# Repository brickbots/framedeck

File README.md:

# framedeck

A Cyberdeck built with the framework mainboard.  

[Framework](https://frame.work) has 
created a really slick, fully user servicable, laptop and have recently started selling the 
[mainboard](https://frame.work/marketplace/mainboards) as a SBC for general 
use.  To better support folks who may want to integrate it into their projects, they are also 
releasing [technical documentation](https://github.com/FrameworkComputer/Mainboard) including 
pinouts, cad models and other resources.

As they were preparing this documentation release, they emailed me to see if I'd be interested
in a collaboration of sorts.  They would provide one of their laptops and some additional modules
for me to build something unique with the only condition being that I released the designs 
for public use.  So here we are!

The mainboard is a great little unit, being a full Intel based system on a single board with 
great storage and memory expansion, decent on-board graphics and full power management.  Since
it was designed to fit into the laptop first and foremost, some of the connectors are fairly
specialized, but with the pinouts available there are a lot of opportunities for expansion. The
board also has four standard USB-C ports which provide many possibilities without even trying
any of the other on-board connectors.

That's all to say that when they reached out and explained their plans and offered to let 
me play with one, I jumped at the chance and this is what I came up with after some experimentation.

It's my take on the slab style computers that were somewhat popular before the world settled
on clamshell designs for portable computers.  I really wanted a 
[TRS-80 model 100](https://en.wikipedia.org/wiki/TRS-80_Model_100) when I was young so this
sort of design was a big influence.

To complete the unit I added battery from the framework laptop, custom mechanical keyboard, wifi card, 
ssd storage, 16gb of memory, 7" IPS display and some speakers in the hopes of making a fairly useful 
computer.  I ended up using the mainboard with their battery rather than roll my own power solution as
it has solid capacity and is already desinged to work with the onboard power management.  For
other uses the mainboard can be powered via USB-C, so a solid powerbank would provide plenty 
of runtime or it can run off any USB-C power brick for stationary use.

For the case, I wanted something interesting that showed off the mainboard, custom keyboard PCB and 
just looked unusual... so clear acrylic and brass won the day!  I thought about 3d printing, and 
I could have done it in several sections, but building the unit up with layers of laser-cut acrylic 
offered some interesting challenges and opportunities.  

Consider this repo a sort of 'guided tour' to give some inspiration and show what might be done with the
framework mainboard.  I'll highlight some things that I think are interesting, or that were tricky, but 
it's not meant to be a comprehensive guide so all the normal caveats apply if you
want to dive in and build something based off this material.  I'm including all of
my design files for reference, but there are lots of details of the build I probably won't cover.  
If you want to build one, or something similar, feel free to reach out and I'd be happy to answer
and questions or provide advice.

* [Build Tour](docs/build_tour.md)
* [Parts List](docs/parts.md)
* [Case Layers](case/layers.md)
* [3d Printed Bits](printed_parts/bits.md)
* [What's with that keyboard?](docs/keyboard.md)

## Copyright and License

Copyright (c) 2022 Richard Sutherland. All rights reserved.

All files are licensed under MIT license or [CC BY-SA 4.0](https://creativecommons.org/licenses/by-sa/4.0/), see the [LICENSE](LICENSE) for more information.

<a href='https://ko-fi.com/brickbots' target='_blank'>

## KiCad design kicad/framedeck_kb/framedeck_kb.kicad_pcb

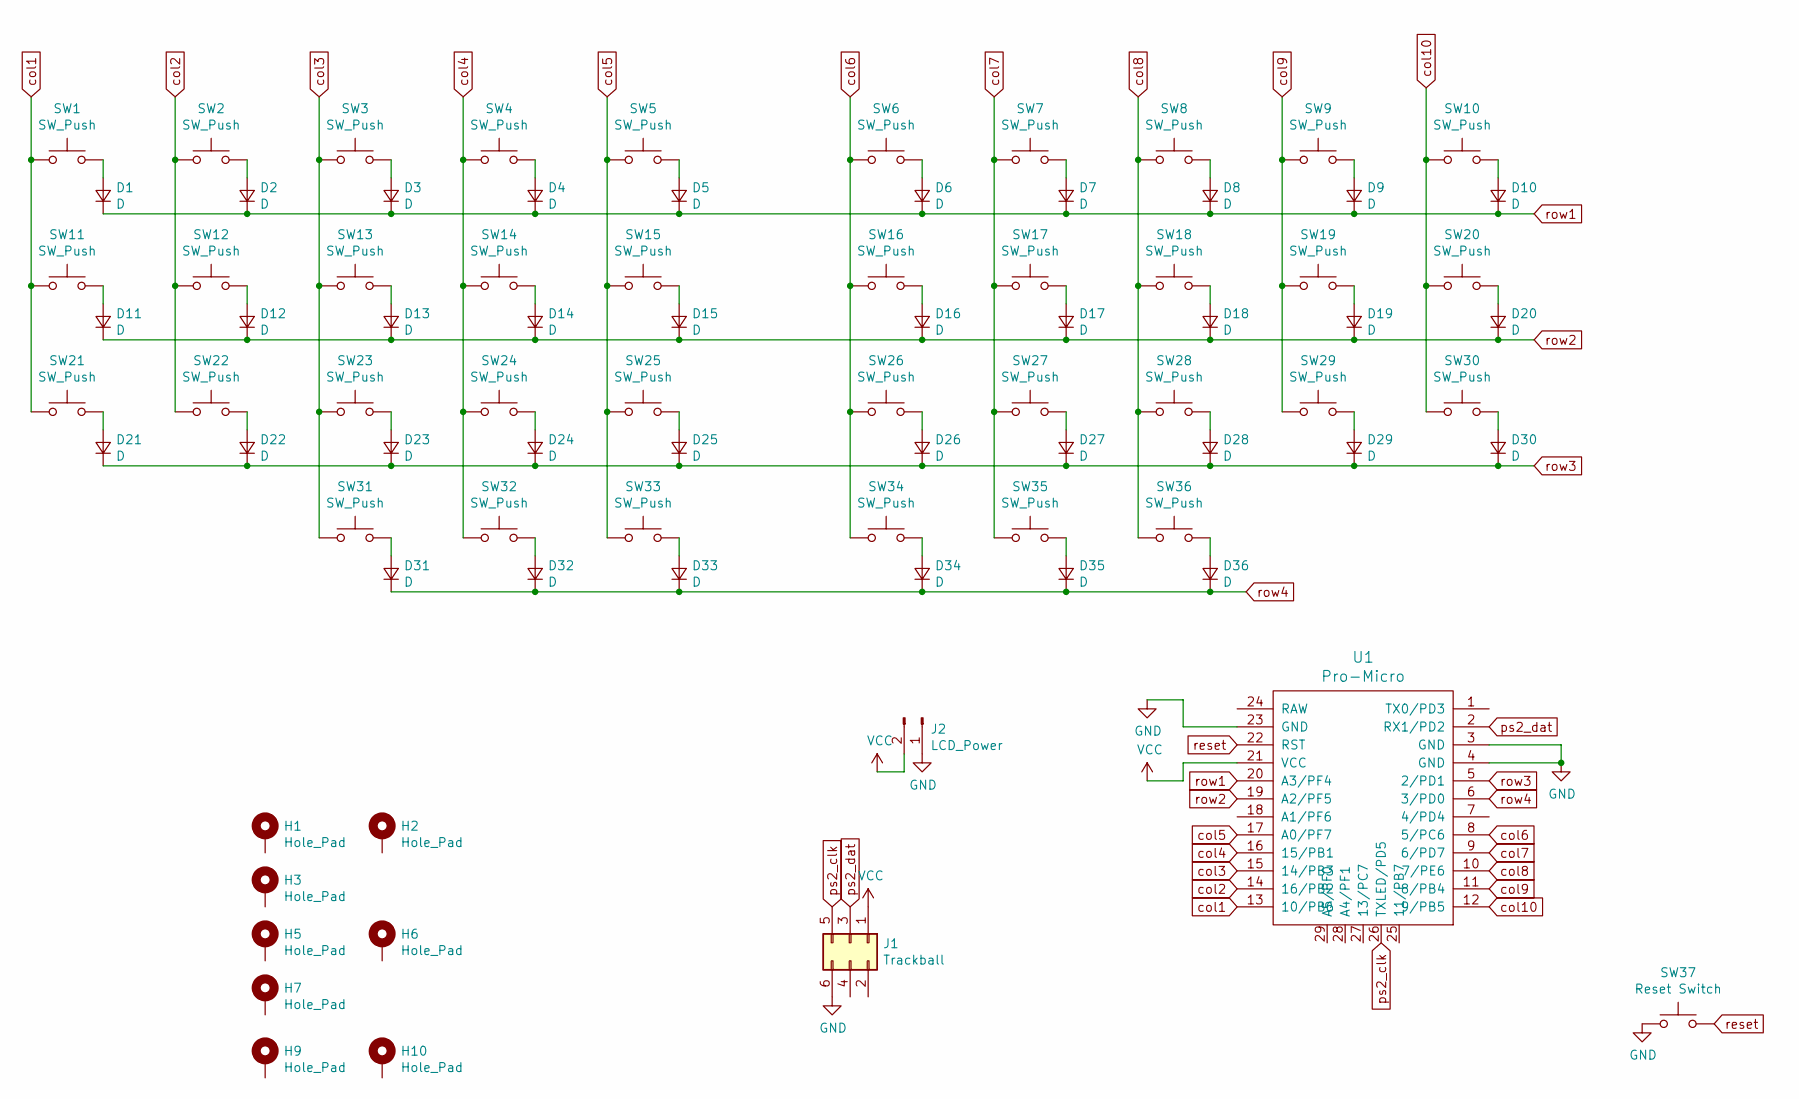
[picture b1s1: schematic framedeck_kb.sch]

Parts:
D1, D2, D3, D4, D5, D6, D7, D8, D9, D10, D11, D12, D13, D14, D15, D16, D17, D18, D19, D20, D21, D22, D23, D24, D25, D26, D27, D28, D29, D30, D31, D32, D33, D34, D35, D36: D; D_SOD-123
H1, H2, H3, H5, H6, H7, H9, H10: Hole_Pad; Mount_M2
J1: Trackball; PinHeader_2x03_P2.00mm_Vertical
J2: LCD_Power; PinHeader_1x02_P2.54mm_Vertical
SW1, SW2, SW3, SW4, SW5, SW6, SW7, SW8, SW9, SW10, SW11, SW12, SW13, SW14, SW15, SW16, SW17, SW18, SW19, SW20, SW21, SW22, SW23, SW24, SW25, SW26, SW27, SW28, SW29, SW30, SW31, SW32, SW33, SW34, SW35, SW36: SW_Push; SW_MX_plate
SW37: Reset Switch; SW_Push_6mm
U1: Pro-Micro; Elite-C

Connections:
GND: J1.6, J2.1, SW37.1, U1.3 (GND), U1.4 (GND), U1.23 (GND)
unnamed: D1.2 (A), SW1.2
unnamed: D2.2 (A), SW2.2
unnamed: D3.2 (A), SW3.2
unnamed: D4.2 (A), SW4.2
unnamed: D5.2 (A), SW5.2
unnamed: D6.2 (A), SW6.2
unnamed: D7.2 (A), SW7.2
unnamed: D8.2 (A), SW8.2
unnamed: D9.2 (A), SW9.2
unnamed: D10.2 (A), SW10.2
unnamed: D11.2 (A), SW11.2
unnamed: D12.2 (A), SW12.2
unnamed: D13.2 (A), SW13.2
unnamed: D14.2 (A), SW14.2
unnamed: D15.2 (A), SW15.2
unnamed: D16.2 (A), SW16.2
unnamed: D17.2 (A), SW17.2
unnamed: D18.2 (A), SW18.2
unnamed: D19.2 (A), SW19.2
unnamed: D20.2 (A), SW20.2
unnamed: D21.2 (A), SW21.2
unnamed: D22.2 (A), SW22.2
unnamed: D23.2 (A), SW23.2
unnamed: D24.2 (A), SW24.2
unnamed: D25.2 (A), SW25.2
unnamed: D26.2 (A), SW26.2
unnamed: D27.2 (A), SW27.2
unnamed: D28.2 (A), SW28.2
unnamed: D29.2 (A), SW29.2
unnamed: D30.2 (A), SW30.2
unnamed: D31.2 (A), SW31.2
unnamed: D32.2 (A), SW32.2
unnamed: D33.2 (A), SW33.2
unnamed: D34.2 (A), SW34.2
unnamed: D35.2 (A), SW35.2
unnamed: D36.2 (A), SW36.2
VCC: J1.1, J2.2, U1.21 (VCC)
col1: SW1.1, SW11.1, SW21.1, U1.13 (10/PB6)
col2: SW2.1, SW12.1, SW22.1, U1.14 (16/PB2)
col3: SW3.1, SW13.1, SW23.1, SW31.1, U1.15 (14/PB3)
col4: SW4.1, SW14.1, SW24.1, SW32.1, U1.16 (15/PB1)
col5: SW5.1, SW15.1, SW25.1, SW33.1, U1.17 (A0/PF7)
col6: SW6.1, SW16.1, SW26.1, SW34.1, U1.8 (5/PC6)
col7: SW7.1, SW17.1, SW27.1, SW35.1, U1.9 (6/PD7)
col8: SW8.1, SW18.1, SW28.1, SW36.1, U1.10 (7/PE6)
col9: SW9.1, SW19.1, SW29.1, U1.11 (8/PB4)
col10: SW10.1, SW20.1, SW30.1, U1.12 (9/PB5)
ps2_clk: J1.5, U1.26 (TXLED/PD5)
ps2_dat: J1.3, U1.2 (RX1/PD2)
reset: SW37.2, U1.22 (RST)
row1: D1.1 (K), D2.1 (K), D3.1 (K), D4.1 (K), D5.1 (K), D6.1 (K), D7.1 (K), D8.1 (K), D9.1 (K), D10.1 (K), U1.20 (A3/PF4)
row2: D11.1 (K), D12.1 (K), D13.1 (K), D14.1 (K), D15.1 (K), D16.1 (K), D17.1 (K), D18.1 (K), D19.1 (K), D20.1 (K), U1.19 (A2/PF5)
row3: D21.1 (K), D22.1 (K), D23.1 (K), D24.1 (K), D25.1 (K), D26.1 (K), D27.1 (K), D28.1 (K), D29.1 (K), D30.1 (K), U1.5 (2/PD1)
row4: D31.1 (K), D32.1 (K), D33.1 (K), D34.1 (K), D35.1 (K), D36.1 (K), U1.6 (3/PD0)

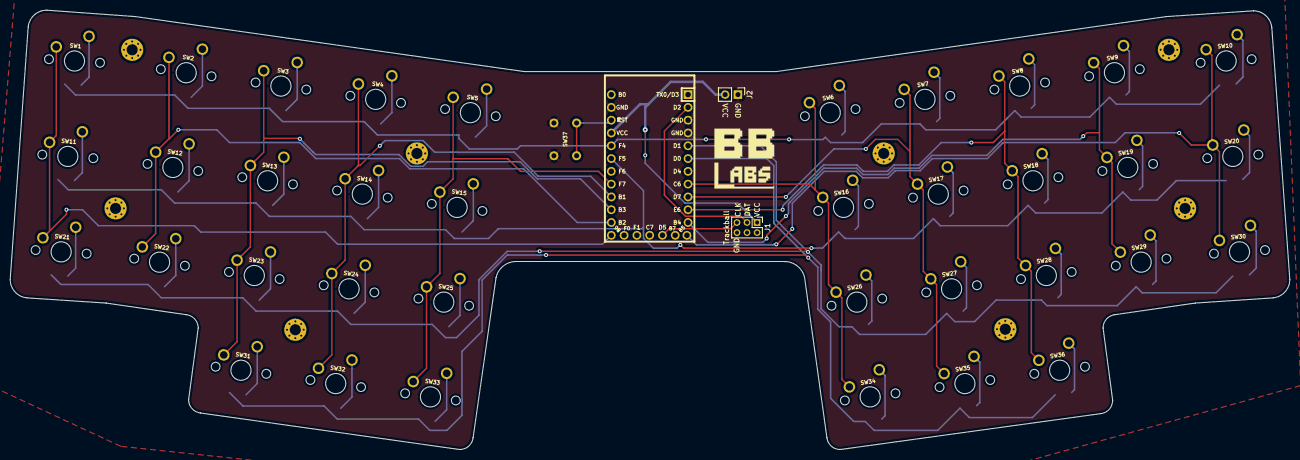
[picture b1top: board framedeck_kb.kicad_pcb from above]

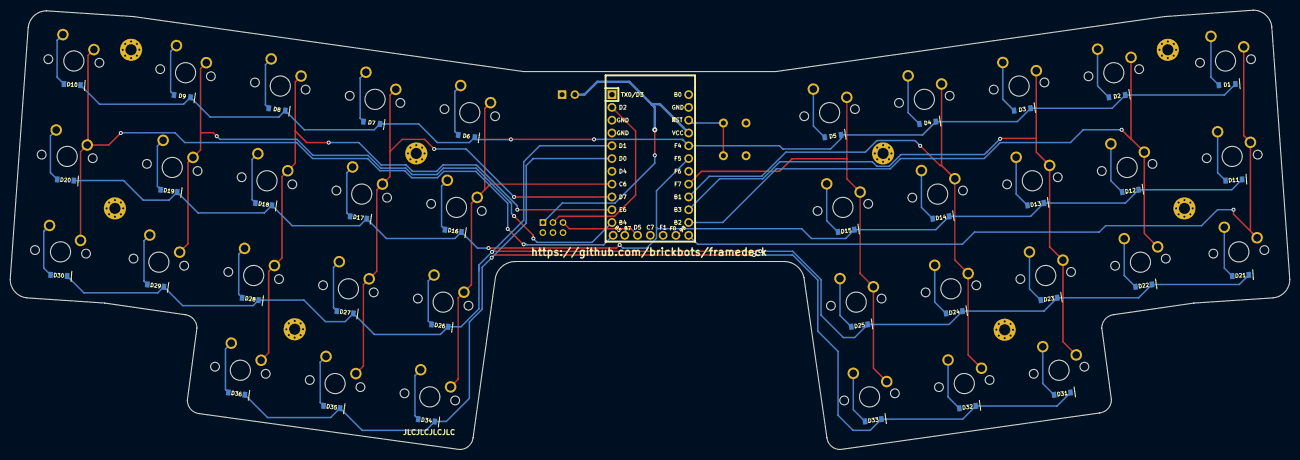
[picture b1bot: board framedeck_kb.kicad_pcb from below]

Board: 2 copper layers, 254.1 x 87.2 mm, 84 parts (37 on the bottom side), 55 nets.

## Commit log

2022-05-11 Starting docs
2022-05-11 Testing images
2022-05-11 Layers
2022-05-11 Fix layers
2022-05-11 Fix links in readme
2022-05-11 Continuing docs
2022-05-15 starting build guide
2022-05-15 Docs draft done
2022-05-15 Added printed docs
2022-05-15 Beauty images
2022-05-15 Fix readme image
2022-05-16 Typo fix s/obard/board
2022-05-16 Fix typos
2022-05-16 Update license for wikimedia friendliness
2022-05-19 Add keyboard info
2023-01-24 Buy me a coffee
2026-05-25 Update README.md
    Fix typo in README.md
